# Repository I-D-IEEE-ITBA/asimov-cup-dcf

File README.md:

# Display Contador Futbol (DCF)

## Descripción

Proyecto del *Display Contador Futbol*, que forma parte del desarrollo de la [Asimov Cup](https://ieeeitba.org.ar/asimovcup) en la competencia de *Futbol*.

DCF permite dar la señal de inicio del partido, cronometrar el tiempo de juego, pausarlo de ser necesario, a la vez que mantiene la cuenta de goles anotados por cada equipo.

El repositorio incluye tanto el hardware como el firmware desarrollado.

----------

<p align="middle">    

</p>

<p align="middle">    

</p>

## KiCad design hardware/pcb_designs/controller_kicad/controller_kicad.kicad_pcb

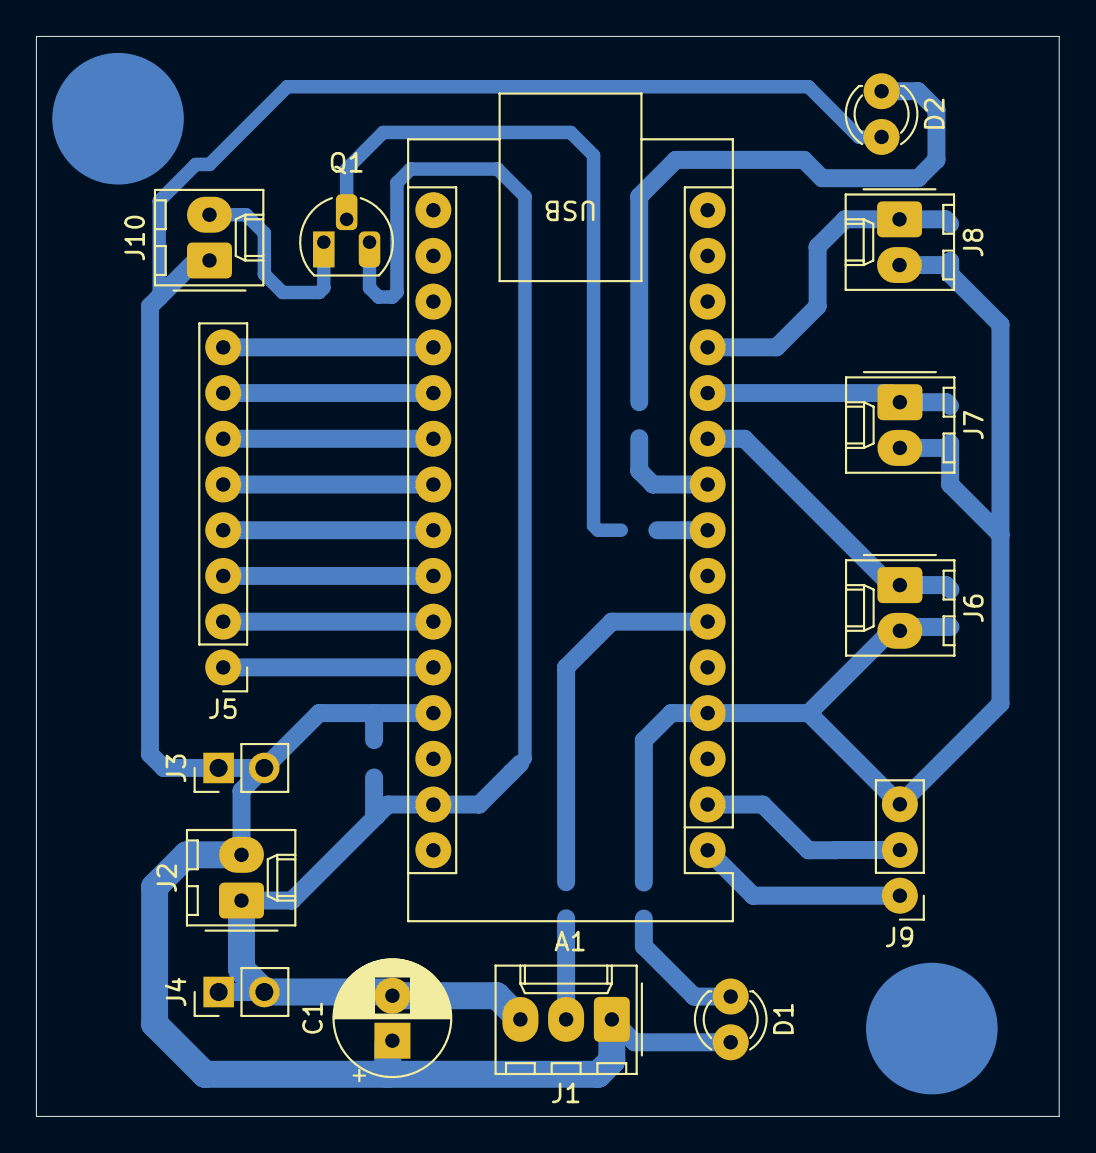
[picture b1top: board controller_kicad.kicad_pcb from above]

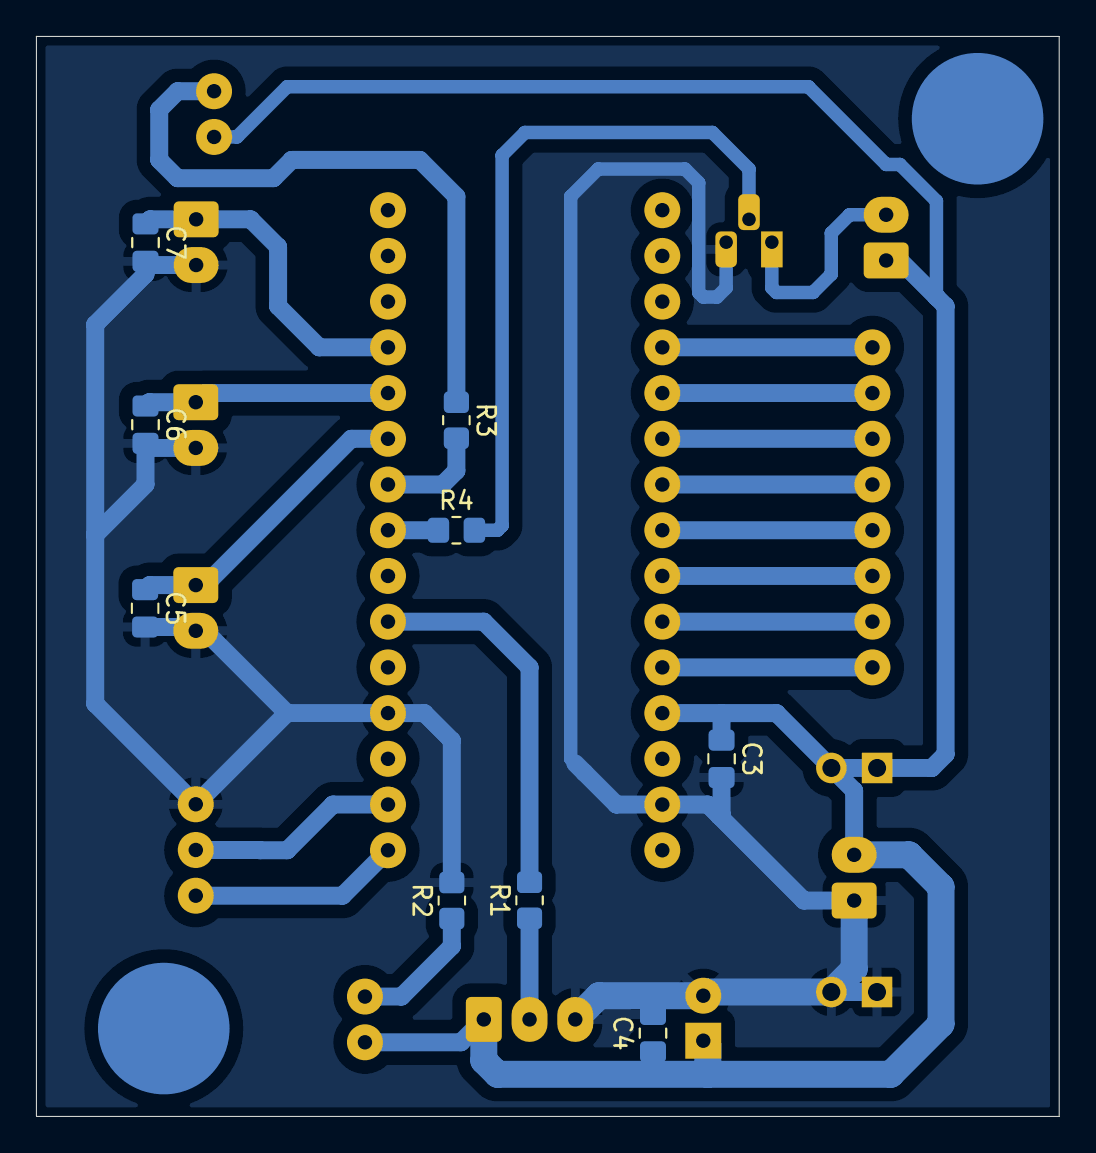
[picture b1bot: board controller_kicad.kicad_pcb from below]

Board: 2 copper layers, 56.8 x 60.0 mm, 24 parts (9 on the bottom side), 23 nets.

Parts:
A1: Arduino_Nano_v3.x; Arduino_Nano
C1: 100u; CP_Radial_D6.3mm_P2.50mm
C3, C4, C5, C6, C7: 1u; C_0805_2012Metric_Pad1.18x1.45mm_HandSolder
D1, D2: LED; LED_D3.0mm
J1: STRIP; Molex_KK-254_AE-6410-03A_1x03_P2.54mm_Vertical
J2: POW; Molex_KK-254_AE-6410-02A_1x02_P2.54mm_Vertical
J3, J4: POW; PinHeader_1x02_P2.54mm_Vertical
J5: ANALOGS; PinHeader_1x08_P2.54mm_Vertical
J6: SW0; Molex_KK-254_AE-6410-02A_1x02_P2.54mm_Vertical
J7: SW1; Molex_KK-254_AE-6410-02A_1x02_P2.54mm_Vertical
J8: SW2; Molex_KK-254_AE-6410-02A_1x02_P2.54mm_Vertical
J9: UART; PinHeader_1x03_P2.54mm_Vertical
J10: BUZZER; Molex_KK-254_AE-6410-02A_1x02_P2.54mm_Vertical
Q1: BC547; TO-92_HandSolder
R1, R2: 330; R_0805_2012Metric_Pad1.20x1.40mm_HandSolder
R3: 680; R_0805_2012Metric_Pad1.20x1.40mm_HandSolder
R4: 2k2; R_0805_2012Metric_Pad1.20x1.40mm_HandSolder

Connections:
+5V: A1.27 (+5V), C1.1, C3.1, C4.1, D1.2 (A), D2.2 (A), J1.1, J2.2, J3.1, J3.2, J10.1
/BUZZER: A1.8 (D5), R4.1
/MISC_LED: A1.9 (D6), R3.2
/RGB_DATA: A1.6 (D3), R1.2
/RX: A1.2 (D0/RX), J9.2
/SCL: A1.24 (A5), J5.3
/SDA: A1.23 (A4), J5.4
/SW0: A1.10 (D7), C5.1, J6.1
/SW1: A1.11 (D8), C6.1, J7.1
/SW2: A1.12 (D9), C7.1, J8.1
/TX: A1.1 (D1/TX), J9.1
GND: A1.4 (GND), A1.29 (GND), C1.2, C3.2, C4.2, C5.2, C6.2, C7.2, J1.3, J2.1, J4.1, J4.2, J6.2, J7.2, J8.2, J9.3, Q1.3 (E), R2.2
unnamed: A1.19 (A0), J5.8
unnamed: A1.20 (A1), J5.7
unnamed: A1.21 (A2), J5.6
unnamed: A1.22 (A3), J5.5
unnamed: A1.25 (A6), J5.2
unnamed: A1.26 (A7), J5.1
unnamed: D1.1 (K), R2.1
unnamed: D2.1 (K), R3.1
unnamed: J1.2, R1.1
unnamed: J10.2, Q1.1 (C)
unnamed: Q1.2 (B), R4.2

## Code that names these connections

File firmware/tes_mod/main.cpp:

/** *************************************************************************************
   
    * @file        main.cpp
    * @brief       Main firmware file for Asimov Cup DCF project with modular architecture
    * @author      IEEE-ITBA | I+D | S. Lopez, A. Heir, J. Torino, I. Dib, J. Pérez
    * @date        2025-05-31
    * @version     2.0
    * @note        This firmware controls button functionality, 7-segment displays, and 
                   RGB LEDs using a modular approach with separate managers for different
                   subsystems. Buttons allow incrementing/decrementing counters, displays
                   show current values.

    ************************************************************************************* */


/* **************************************************************************************
    * INCLUDES AND CONFIGURATION *
   ************************************************************************************** */

#include <Arduino.h>
#include <FastLED.h>

#include "buttons.h"
#include "segments.h"
#include "sound.h"


//* DEBUG CONFIGURATION

#define DEBUG

#ifdef DEBUG
    #ifndef BAUD_RATE
        #define BAUD_RATE 115200
    #endif // BAUD_RATE
    #define DEBUG_PRINT(x) Serial.print(x)
    #define DEBUG_PRINTLN(x) Serial.println(x)
#else
    #define DEBUG_PRINT(x)
    #define DEBUG_PRINTLN(x)
#endif // DEBUG


/* **************************************************************************************
    * CONSTANTS AND DEFINITIONS *
   ************************************************************************************** */

//* HARDWARE PIN DEFINITIONS

#define PIN_RGB_DATA 3                 // WS2812B LED strip data pin
#define PIN_BUZZER 5                   // Buzzer/speaker pin
#define PIN_SW0 7                      // Player 1 button pin
#define PIN_SW1 8                      // Player 2 button pin
#define PIN_SW2 9                      // Reserved button pin (unused)
#define PIN_LED_BUILTIN LED_BUILTIN    // Built-in LED pin
#define PIN_MISC_LED 6                 // Miscellaneous LED pin


//* SYSTEM CONFIGURATION

#define DEFAULT_BRIGHTNESS 100         // Default LED brightness level


/* **************************************************************************************
    * GLOBAL VARIABLES *
   ************************************************************************************** */

//* GAME STATE VARIABLES

int count_p1 = 0;                      // Player 1 counter value
int count_p2 = 0;                      // Player 2 counter value


//* SYSTEM MANAGERS

CRGB leds[NUM_LEDS];                   // LED array for displays
ButtonManager buttonManager(PIN_SW0, PIN_SW1);
DisplayManager displayManager(leds);
SoundManager soundManager(PIN_BUZZER);


/* **************************************************************************************
    * CORE SYSTEM FUNCTIONS *
   ************************************************************************************** */

void setup() 
{
    #ifdef DEBUG
        Serial.begin(BAUD_RATE);
        DEBUG_PRINTLN("Asimov Cup DCF - Starting initialization...");
    #endif

    initializeHardware();
    updateDisplays();
    
    DEBUG_PRINTLN("Initialization complete. System ready.");
    delay(100);
}

void loop() 
{
    handleButtonEvents();
    soundManager.tick();               // Update sound system
    delay(10);                         // Main loop delay
}


//* HARDWARE MANAGEMENT

void initializeHardware() 
{
    // Initialize LED strip and display system
    FastLED.addLeds<WS2812B, PIN_RGB_DATA, GRB>(leds, NUM_LEDS).setCorrection(TypicalLEDStrip);
    displayManager.initialize(DEFAULT_BRIGHTNESS);
    
    // Initialize input and sound systems
    buttonManager.initialize();
    soundManager.initialize();
    
    // Configure additional pins
    pinMode(PIN_SW2, INPUT_PULLUP);      // Reserved button (not used)
    pinMode(PIN_MISC_LED, OUTPUT);       // Miscellaneous LED
    pinMode(PIN_LED_BUILTIN, OUTPUT);    // Built-in LED
    
    // Set initial LED states
    digitalWrite(PIN_MISC_LED, HIGH);
    digitalWrite(PIN_LED_BUILTIN, LOW);
    
    DEBUG_PRINTLN("Hardware initialization complete.");
}


//* EVENT HANDLING

void handleButtonEvents() 
{
    ButtonEvent event = buttonManager.processButtons();
    
    switch (event) 
    {
        case EVENT_SHORT_PRESS_P1:
            DEBUG_PRINTLN("Short press P1");
            count_p1++;
            count_p1 = (count_p1 > 99) ? 99 : count_p1;  // Clamp to maximum
            soundManager.playSound(SOUND_SHORT_PRESS);
            updateDisplays();
            break;
            
        case EVENT_LONG_PRESS_P1:
            DEBUG_PRINTLN("Long press P1");
            count_p1--;
            count_p1 = (count_p1 < 0) ? 0 : count_p1;    // Clamp to minimum
            soundManager.playSound(SOUND_LONG_PRESS);
            updateDisplays();
            break;
            
        case EVENT_SHORT_PRESS_P2:
            DEBUG_PRINTLN("Short press P2");
            count_p2++;
            count_p2 = (count_p2 > 99) ? 99 : count_p2;  // Clamp to maximum
            soundManager.playSound(SOUND_SHORT_PRESS);
            updateDisplays();
            break;
            
        case EVENT_LONG_PRESS_P2:
            DEBUG_PRINTLN("Long press P2");
            count_p2--;
            count_p2 = (count_p2 < 0) ? 0 : count_p2;    // Clamp to minimum
            soundManager.playSound(SOUND_LONG_PRESS);
            updateDisplays();
            break;
            
        case EVENT_BOTH_LONG_PRESS:
            DEBUG_PRINTLN("Both buttons long press - Reset counters");
            count_p1 = 0;
            count_p2 = 0;
            soundManager.playSound(SOUND_DOUBLE_PRESS);
            updateDisplays();
            break;
            
        default:
            // No event occurred, continue normal operation
            break;
    }
    
    // Debug output for counter values when changed
    if (event != EVENT_NONE) 
    {
        DEBUG_PRINT("Counter P1: ");
        DEBUG_PRINT(count_p1);
        DEBUG_PRINT(" | Counter P2: ");
        DEBUG_PRINTLN(count_p2);
    }
}


//* DISPLAY MANAGEMENT

void updateDisplays() 
{
    displayManager.updateDisplays(count_p1, count_p2);
}

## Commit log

2024-07-05 starting controller PCB, preparing directories
2024-07-06 controller PCB finished
2024-07-27 testing 7segments abstraction for ws2812b modules, bySanti
2024-07-27 add elemental full firmware w/ button interactions, w/o {buzzer, visual effects}
2024-07-27 add fancy main README
2024-07-29 3rd button, goals vs timer scenes
2024-07-29 fix pin assignments, tweak processButtons, add debug info
2024-07-29 Agregado un delay en el loop principal para mejorar la consistencia en la detección de pulsaciones
2024-08-02 Agregado el sound manager. Soporta los numeros al reves
2025-05-30 Attempt to modularize the program, need to improve file structure
2025-05-30 Improved file structure, testing still required
2025-05-31 Configured 'dual_score_display_io' folder to be used with the PlatformIO extension
